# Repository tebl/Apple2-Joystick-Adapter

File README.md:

# Apple ][ Joystick Adapter
I have an Apple //e somewhere in my storage room, I don't play on the thing much. Part of the reason might be the lack of a joystick, so I've been attempting to remedy that by soldering something together - the hard, and quite possibly the only real classic way, by reading about them in an old book and attempt to actually build the thing (Computer Controller Cookbook).

The adapter allows you to connect up to two Atari-style joysticks up to the Apple //e, if you like that sort of thing. I'm told most Apple fans prefer their joysticks to be analog because that was all the rage was all about at the end of the 70s, but as already mentioned I don't have one - I on the other hand have a ton of Atari-style joysticks so those are the ones I'd like to use. Keep reading for all the necessary details, click links below if you want to skip to a specific section.

- [1> Building the adapter](#1-building-the-adapter)
  - [1.2> IDC-cables](#12-idc-cables)
  - [1.3> Testing it out](#13-testing-it-out)
- [2> BOM](#2-bom)
  - [2.1> Miscellaneous components](#21-miscellaneous-components)

**NB!** I don't have any of the other variants of the Apple ][ computer than the //e, so I've not been able to test the design on any other variant. I can't tell you wether they work or even fit into them.

# 1> Building the adapter
Building the adapter, as with most things that deals with electronic projects, starts with going through the [BOM](#2-bom) and ordering whatever you don't already have. Compare with the gallery pictures if you're wondering what something looks like, unfortunately ebay is not a good place to shop for well-described components - I usually just order one of each if they're cheap (it'll get used sometime, if only to irritate someone attempting to build more than one of my projects).

Next up is soldering the resistors, these are have the lowest profile of the components and move up in size from that point forward. Please use sockets though, mainly because everything that looks like ICs from ebay can and should be considered highly suspicious until verified working - you will likely want the ability to quickly change one of them out (often they are B-grade or forcibly pulled from other hardware; they may or may not working depending on your luck).

The last component to get soldered into place are the machined pin headers that go into the area labelled A1, these go into the Game I/O socket on the Apple ][ motherboard - the regular kind will probably break your socket, so don't use those (even if they are cheap). They are soldered on the reverse side compared to the other components, to ensure that they are soldered into place at a reasonable angle, I recommend using a 16 pin machined pin socket as a template below the pins.

The last step I usually do with my boards, is installing an M3 nylon standoff (10mm length) into the hole between the IDC connectors - this is there so that there is some strain relief for the pins that go into the socket. It just pushes against the motherboard, so don't use the brass one as that might accidentally short something.

Onto the next step, because everyone loves making cables.

## 1.2> IDC-cables
While I would have liked to just use something that could be ordered straight from AliExpress without going so far as creating a custom cable, all of the ones I've found were mostly IDC to RS232 adapters - those have a rather randomized pin layout so I chose not to use them in the design. The method I used instead was order said cables, cut off the DB9 part already on there and then just add a new male DB9 IDC connector so that pin 1 with pin 1 on both sides (red stripe).

The flat ribbon DB9 connector is easy to use, just push the ribbon through and align - then push down on it with something hard like the handle of a screwdriver (if you don't have a vise). Wrap the cable over, clip the strain relief over the top. The result you should end up with looks like the following, note the position of the tab in relation to the red wire on both sides.

If also adding the 2x5pin straight pin IDC to the other side, then it will have a spot for the tenth wire, this is left empty as we only use nine for the DB9. The process for fixing it into place is the same as before, but there is probably no strain relief this time - so align it according to picture above

Screw the IDC-connector into the case using M3-screws, I mainly use those that come with the cables if you got them (M3x6mm hex standoff, brass or otherwise as long as the cable is firmly in place).

# 1.3> Testing it out
Testing it out is easy, just make sure that it is installed properly - align the back pins with the holes on the socket then push it gently into place. As long as it is aligned properly, you shouldn't need to use more than a little bit of force - anything more and you'll just snap off or bend the header pins. Plug your joystick into what is marked port 1, the one closest to the side of the case, via the cable you just made and mounted on the case.

At this point you can just try to load up a game and see if that works, but personally I like to test it out using some basic code first - if only to see that all the directions work as expected. There is an [article](https://devonhubner.org/check_if_the_appleii_joystick_is_working_using_applesoft_basic/) on Devon Hubners page that does this very nicely and goes into more detail, so just type in the simple version for now and run it (I've posted a copy of it below in case that page disappears).
```
10 PRINT PDL(0), PDL(1)
20 GOTO 10
```
The little piece of code should print the X-value followed by the Y-value on the first port, it should be a number between 0 and 255. When not pushing anything it should center about the mid-point of this, mine was around 140 in values and worked nicely in the games I've tested (mostly Donkey Kong). If you get something significantly different, ensure that the correct value resistors went into the correct place (a swapped 68k and 100k would give 200, as I accidentally found out).

# 2> BOM
This is the list of parts that you'd need in order to construct Apple ][ Joystick Adapter, most could quite possibly be sourced from your friendly neighbourhood electronics store - if you should happen to have one available (using a passport on the way doesn't count). I don't, so I order most of the components on ebay and similar sources - parts may be cheap, but at least you'll need extras in order to assure at least one of them works.

| Reference            | Item                                              | Count |
| -------------------- | ------------------------------------------------- | ----- |
| Adapter (PCB)        | Fabricate using Gerber files ([order](https://www.pcbway.com/project/shareproject/Apple___e_Joystick_Adapter.html))          |     1 |
| A1 *                 | 8 pin machined pin header                         |     2 |    
| C1,C2                | 100nF ceramic capacitor (5mm)                     |     2 |
| C3                   | 4.7uF electrolytic capacitor (2mm)                |     1 |
| IC1                  | 74HCT04 (DIP-14)                                  |     1 |
| IC2                  | CD4066 (DIP-14)                                   |     1 |
| J1,J2                | 2x5 pin straight IDC socket                       |     2 |
| R1-R6                | 1k Ohm resistor                                   |     6 |
| R7-R10               | 68k Ohm resistor                                  |     4 |
| R11-R14              | 100k Ohm resistor                                 |     4 |

*) These are soldered on the reverse side compared to the other components, these pins go into the Game I/O socket on the Apple ][ motherboard. These are usually sold as 40 pin breakable strips, it is recommended to use the machined pin headers as they won't destroy the motherboard socket like the regular pin header eventually would.

## 2.1> Miscellaneous components
This is a suggested list of components used to screw together each of the PCBs, most of these you can find as part of a set on ebay (just search for "*M3 nylon assorted standoff kit*"). Cable components are also listed here.

| Reference | Item                                      | Count |
| --------- | ----------------------------------------- | ----- |
|           | M3x6mm nylon screw                        |     1 |
|           | M3x10mm Nylon Hex standoff                |     1 |
|           | IDC Flat Ribbon DB9 Male Connector        |     2 |
|           | 2x5 Flat Riboon IDC Connector             |     2 |
|           | 9 core flat ribbon cable                  |     2 |

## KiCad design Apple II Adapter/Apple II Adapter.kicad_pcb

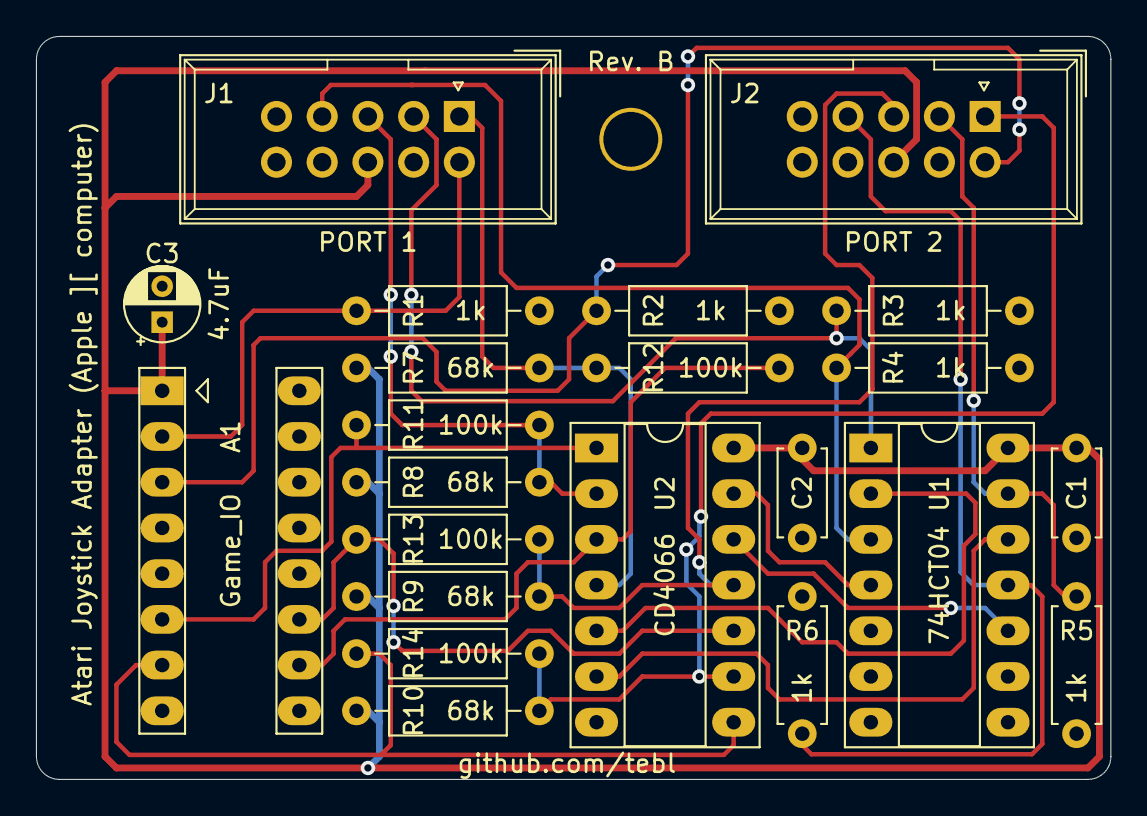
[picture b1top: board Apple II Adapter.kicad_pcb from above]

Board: 2 copper layers, 59.7 x 41.3 mm, 23 parts (0 on the bottom side), 20 nets.

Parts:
A1: Game_IO; DIP-16_W7.62mm_Socket_LongPads
C1, C2: 100nF; C_Disc_D4.7mm_W2.5mm_P5.00mm
C3: 4.7uF; CP_Radial_D4.0mm_P2.00mm
J1: IDC_PORT1; IDC_Joystick
J2: IDC_PORT2; IDC_Joystick
M1: Mounting; M3_pin
R1, R2, R3, R4: 1k; R_Axial_DIN0207_L6.3mm_D2.5mm_P10.16mm_Horizontal
R5, R6: 1k; R_Axial_DIN0207_L6.3mm_D2.5mm_P7.62mm_Horizontal
R7, R8, R9, R10: 68k; R_Axial_DIN0207_L6.3mm_D2.5mm_P10.16mm_Horizontal
R11, R12, R13, R14: 100k; R_Axial_DIN0207_L6.3mm_D2.5mm_P10.16mm_Horizontal
U1: 74HCT04; DIP-14_W7.62mm_Socket_LongPads
U2: CD4066; DIP-14_W7.62mm_Socket_LongPads

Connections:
/GC0: A1.6, R11.1, U2.1
/GC1: A1.10, R12.1, U2.3
/GC2: A1.7, R14.1, U2.8
/GC3: A1.11, R13.1, U2.10
/P1_DOWN: J1.2, R3.2, U1.1
/P1_FIRE: A1.2, J1.6, R1.2
/P1_LEFT: J1.3, R8.1, R11.2, U2.2
/P1_RIGHT: J1.4, R4.2, U1.3
/P1_UP: J1.1, R7.1, R12.2, U2.4
/P2_DOWN: J2.2, R5.2, U1.13
/P2_FIRE: A1.3, J2.6, R2.2
/P2_LEFT: J2.3, R9.1, R13.2, U2.11
/P2_RIGHT: J2.4, R6.2, U1.11
/P2_UP: J2.1, R10.1, R14.2, U2.9
GND: A1.8, C1.2, C2.2, C3.2, R1.1, R2.1, R3.1, R4.1, R5.1, R6.1, U1.5, U1.7, U1.9, U2.7
unnamed: U1.2, U2.5
unnamed: U1.4, U2.13
unnamed: U1.10, U2.12
unnamed: U1.12, U2.6
VCC: A1.1, C1.1, C2.1, C3.1, J1.8, J2.8, R7.2, R8.2, R9.2, R10.2, U1.14, U2.14

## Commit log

2021-01-09 Added adapter schematic
2021-01-09 Assigned footprints
2021-01-10 Layout routed
2021-01-19 Minor silkscreen changes
2021-01-29 Added README
2021-01-29 Added license label
2021-01-31 Fixed revision A bugs (label and joystick common)
2021-02-01 Swapped fire buttons
2021-02-01 Added images
2021-02-01 Removed leftover notes
2021-02-01 Cable pictures
2021-02-01 Improved cable description
2021-02-01 Added test section to README

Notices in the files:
Apple II Adapter/Apple II Adapter.kicad_pcb:
Licensed under
CERN OHL v1.2
